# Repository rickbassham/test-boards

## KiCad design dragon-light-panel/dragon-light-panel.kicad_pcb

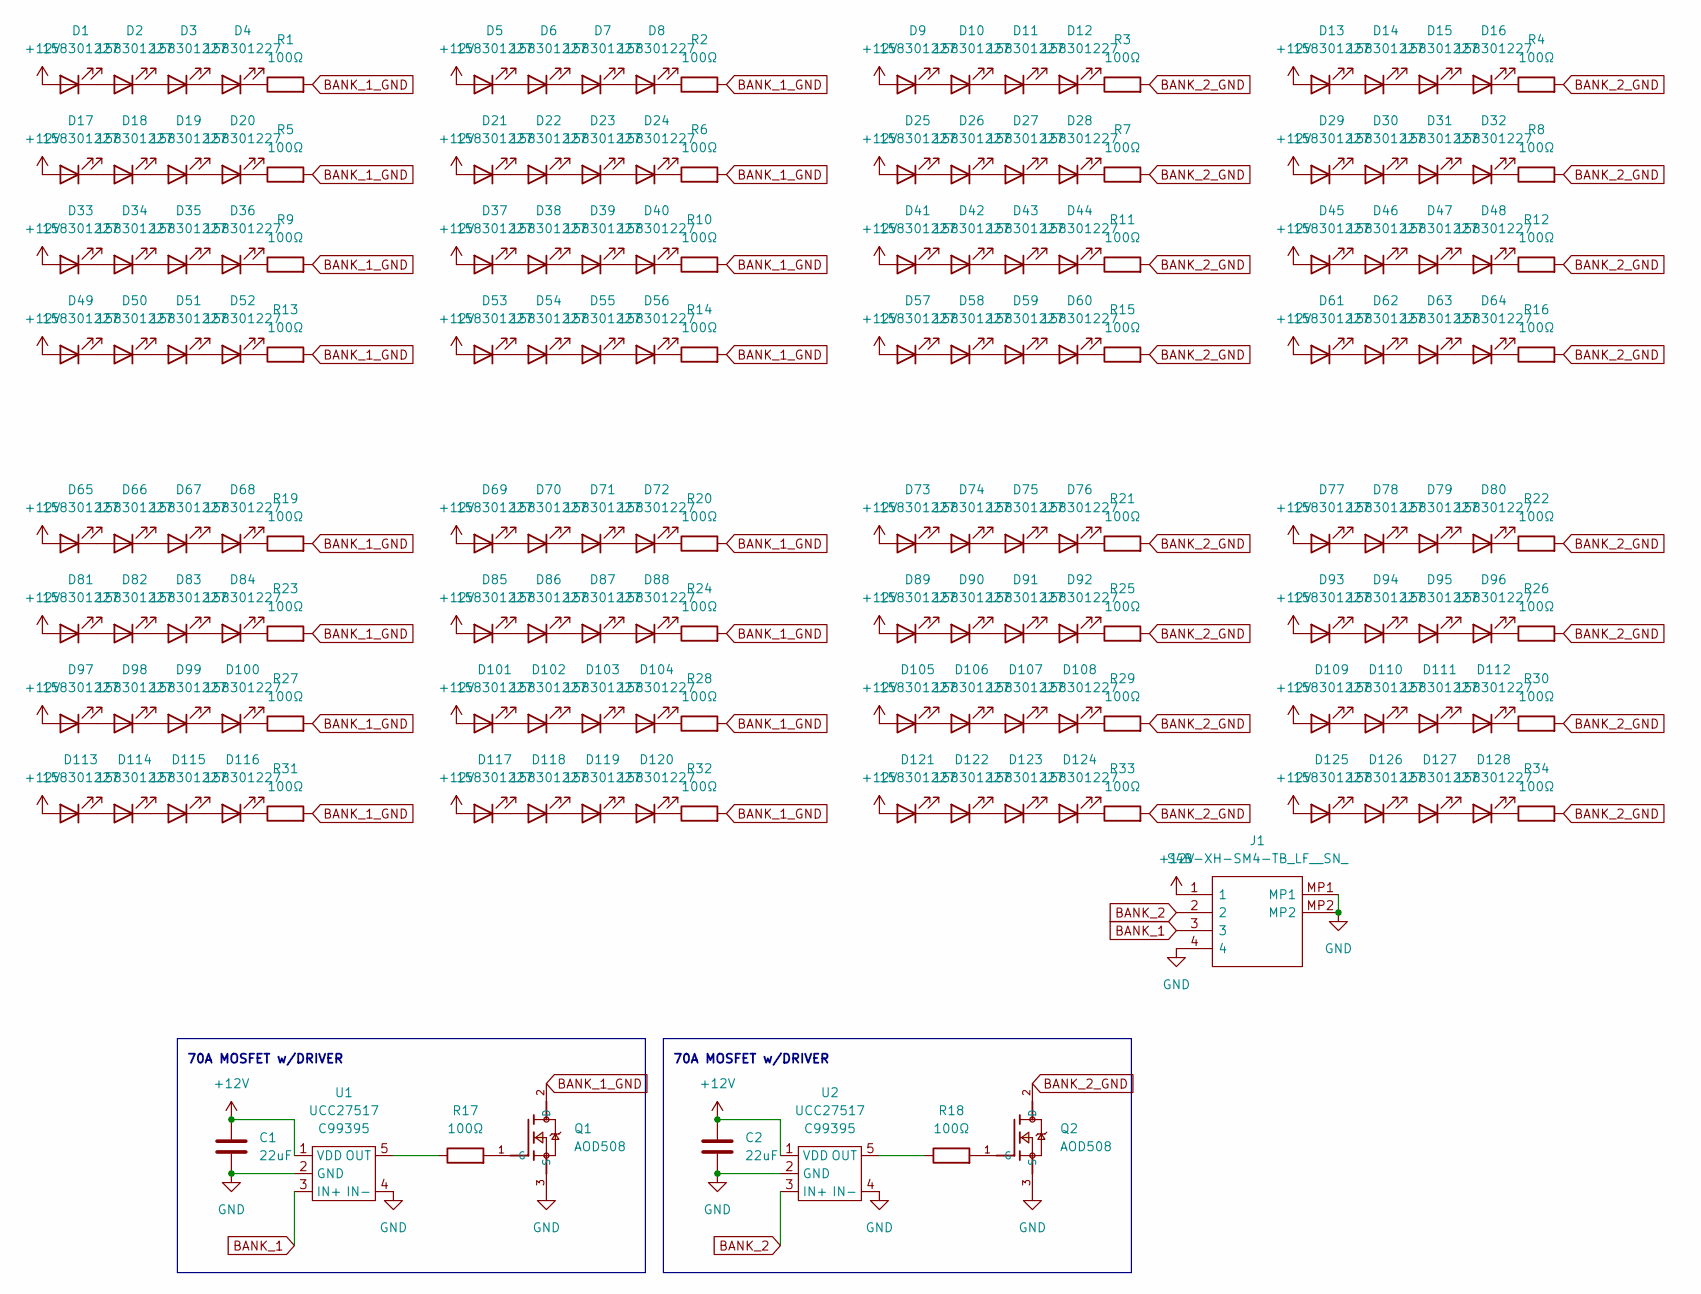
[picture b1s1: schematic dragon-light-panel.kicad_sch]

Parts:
C1, C2: 22uF; C_0805_2012Metric; LCSC C45783
D1, D2, D3, D4, D5, D6, D7, D8, D9, D10, D11, D12, D13, D14, D15, D16, D17, D18, D19, D20, D21, D22, D23, D24, D25, D26, D27, D28, D29, D30, D31, D32, D33, D34, D35, D36, D37, D38, D39, D40, D41, D42, D43, D44, D45, D46, D47, D48, D49, D50, D51, D52, D53, D54, D55, D56, D57, D58, D59, D60, D61, D62, D63, D64, D65, D66, D67, D68, D69, D70, D71, D72, D73, D74, D75, D76, D77, D78, D79, D80, D81, D82, D83, D84, D85, D86, D87, D88, D89, D90, D91, D92, D93, D94, D95, D96, D97, D98, D99, D100, D101, D102, D103, D104, D105, D106, D107, D108, D109, D110, D111, D112, D113, D114, D115, D116, D117, D118, D119, D120, D121, D122, D123, D124, D125, D126, D127, D128: 158301227; LED_1206_3216Metric; JLCPCB Class E
J1: S4B-XH-SM4-TB_LF__SN_; S4BXHSM4TBLFSN; LCSC C161861
Q1, Q2: AOD508; TO-252-2; LCSC C80964
R1, R2, R3, R4, R5, R6, R7, R8, R9, R10, R11, R12, R13, R14, R15, R16, R19, R20, R21, R22, R23, R24, R25, R26, R27, R28, R29, R30, R31, R32, R33, R34: 100Ω; R_1206_3216Metric; LCSC C17901
R17, R18: 100Ω; R_0402_1005Metric; LCSC C25076
U1, U2: UCC27517; SOT-23-5; LCSC C99395

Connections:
+12V: C1.1, C2.1, D1.2 (A), D5.2 (A), D9.2 (A), D13.2 (A), D17.2 (A), D21.2 (A), D25.2 (A), D29.2 (A), D33.2 (A), D37.2 (A), D41.2 (A), D45.2 (A), D49.2 (A), D53.2 (A), D57.2 (A), D61.2 (A), D65.2 (A), D69.2 (A), D73.2 (A), D77.2 (A), D81.2 (A), D85.2 (A), D89.2 (A), D93.2 (A), D97.2 (A), D101.2 (A), D105.2 (A), D109.2 (A), D113.2 (A), D117.2 (A), D121.2 (A), D125.2 (A), J1.1, U1.1 (VDD), U2.1 (VDD)
BANK_1: J1.3, U1.3 (IN+)
BANK_1_GND: Q1.2 (D), R1.2, R2.2, R5.2, R6.2, R9.2, R10.2, R13.2, R14.2, R19.2, R20.2, R23.2, R24.2, R27.2, R28.2, R31.2, R32.2
BANK_2: J1.2, U2.3 (IN+)
BANK_2_GND: Q2.2 (D), R3.2, R4.2, R7.2, R8.2, R11.2, R12.2, R15.2, R16.2, R21.2, R22.2, R25.2, R26.2, R29.2, R30.2, R33.2, R34.2
GND: C1.2, C2.2, J1.4, J1.MP1, J1.MP2, Q1.3 (S), Q2.3 (S), U1.2 (GND), U1.4 (IN-), U2.2 (GND), U2.4 (IN-)
unnamed: D1.1 (K), D2.2 (A)
unnamed: D2.1 (K), D3.2 (A)
unnamed: D3.1 (K), D4.2 (A)
unnamed: D4.1 (K), R1.1
unnamed: D5.1 (K), D6.2 (A)
unnamed: D6.1 (K), D7.2 (A)
unnamed: D7.1 (K), D8.2 (A)
unnamed: D8.1 (K), R2.1
unnamed: D10.1 (K), D11.2 (A)
unnamed: D9.1 (K), D10.2 (A)
unnamed: D11.1 (K), D12.2 (A)
unnamed: D12.1 (K), R3.1
unnamed: D13.1 (K), D14.2 (A)
unnamed: D14.1 (K), D15.2 (A)
unnamed: D15.1 (K), D16.2 (A)
unnamed: D16.1 (K), R4.1
unnamed: D17.1 (K), D18.2 (A)
unnamed: D18.1 (K), D19.2 (A)
unnamed: D19.1 (K), D20.2 (A)
unnamed: D20.1 (K), R5.1
unnamed: D21.1 (K), D22.2 (A)
unnamed: D22.1 (K), D23.2 (A)
unnamed: D23.1 (K), D24.2 (A)
unnamed: D24.1 (K), R6.1
unnamed: D25.1 (K), D26.2 (A)
unnamed: D26.1 (K), D27.2 (A)
unnamed: D27.1 (K), D28.2 (A)
unnamed: D28.1 (K), R7.1
unnamed: D29.1 (K), D30.2 (A)
unnamed: D30.1 (K), D31.2 (A)
unnamed: D31.1 (K), D32.2 (A)
unnamed: D32.1 (K), R8.1
unnamed: D33.1 (K), D34.2 (A)
unnamed: D34.1 (K), D35.2 (A)
unnamed: D35.1 (K), D36.2 (A)
unnamed: D36.1 (K), R9.1
unnamed: D37.1 (K), D38.2 (A)
unnamed: D38.1 (K), D39.2 (A)
unnamed: D39.1 (K), D40.2 (A)
unnamed: D40.1 (K), R10.1
unnamed: D41.1 (K), D42.2 (A)
unnamed: D42.1 (K), D43.2 (A)
unnamed: D43.1 (K), D44.2 (A)
unnamed: D44.1 (K), R11.1
unnamed: D45.1 (K), D46.2 (A)
unnamed: D46.1 (K), D47.2 (A)
unnamed: D47.1 (K), D48.2 (A)
unnamed: D48.1 (K), R12.1
unnamed: D49.1 (K), D50.2 (A)
unnamed: D50.1 (K), D51.2 (A)
unnamed: D51.1 (K), D52.2 (A)
unnamed: D52.1 (K), R13.1
unnamed: D53.1 (K), D54.2 (A)
unnamed: D54.1 (K), D55.2 (A)
unnamed: D55.1 (K), D56.2 (A)
unnamed: D56.1 (K), R14.1
unnamed: D57.1 (K), D58.2 (A)
unnamed: D58.1 (K), D59.2 (A)
unnamed: D59.1 (K), D60.2 (A)
unnamed: D60.1 (K), R15.1
unnamed: D61.1 (K), D62.2 (A)
unnamed: D62.1 (K), D63.2 (A)
unnamed: D63.1 (K), D64.2 (A)
unnamed: D64.1 (K), R16.1
unnamed: D65.1 (K), D66.2 (A)
unnamed: D66.1 (K), D67.2 (A)
unnamed: D67.1 (K), D68.2 (A)
unnamed: D68.1 (K), R19.1
unnamed: D69.1 (K), D70.2 (A)
unnamed: D70.1 (K), D71.2 (A)
unnamed: D71.1 (K), D72.2 (A)
unnamed: D72.1 (K), R20.1
unnamed: D73.1 (K), D74.2 (A)
unnamed: D74.1 (K), D75.2 (A)
unnamed: D75.1 (K), D76.2 (A)
unnamed: D76.1 (K), R21.1
unnamed: D77.1 (K), D78.2 (A)
unnamed: D78.1 (K), D79.2 (A)
unnamed: D79.1 (K), D80.2 (A)
unnamed: D80.1 (K), R22.1
unnamed: D81.1 (K), D82.2 (A)
unnamed: D82.1 (K), D83.2 (A)
unnamed: D83.1 (K), D84.2 (A)
unnamed: D84.1 (K), R23.1
unnamed: D85.1 (K), D86.2 (A)
unnamed: D86.1 (K), D87.2 (A)
unnamed: D87.1 (K), D88.2 (A)
unnamed: D88.1 (K), R24.1
unnamed: D89.1 (K), D90.2 (A)
unnamed: D90.1 (K), D91.2 (A)
unnamed: D91.1 (K), D92.2 (A)
unnamed: D92.1 (K), R25.1
unnamed: D93.1 (K), D94.2 (A)
unnamed: D94.1 (K), D95.2 (A)
unnamed: D95.1 (K), D96.2 (A)
unnamed: D96.1 (K), R26.1
unnamed: D97.1 (K), D98.2 (A)
unnamed: D98.1 (K), D99.2 (A)
unnamed: D100.1 (K), R27.1
unnamed: D99.1 (K), D100.2 (A)
unnamed: D101.1 (K), D102.2 (A)
unnamed: D102.1 (K), D103.2 (A)
unnamed: D103.1 (K), D104.2 (A)
unnamed: D104.1 (K), R28.1
unnamed: D105.1 (K), D106.2 (A)
unnamed: D106.1 (K), D107.2 (A)
unnamed: D107.1 (K), D108.2 (A)
unnamed: D108.1 (K), R29.1
unnamed: D109.1 (K), D110.2 (A)
unnamed: D110.1 (K), D111.2 (A)
unnamed: D111.1 (K), D112.2 (A)
unnamed: D112.1 (K), R30.1
unnamed: D113.1 (K), D114.2 (A)
unnamed: D114.1 (K), D115.2 (A)
unnamed: D115.1 (K), D116.2 (A)
unnamed: D116.1 (K), R31.1
unnamed: D117.1 (K), D118.2 (A)
unnamed: D118.1 (K), D119.2 (A)
unnamed: D119.1 (K), D120.2 (A)
unnamed: D120.1 (K), R32.1
unnamed: D121.1 (K), D122.2 (A)
unnamed: D122.1 (K), D123.2 (A)
unnamed: D123.1 (K), D124.2 (A)
unnamed: D124.1 (K), R33.1
unnamed: D125.1 (K), D126.2 (A)
unnamed: D126.1 (K), D127.2 (A)
unnamed: D127.1 (K), D128.2 (A)
unnamed: D128.1 (K), R34.1
unnamed: Q1.1 (G), R17.2
unnamed: Q2.1 (G), R18.2
unnamed: R17.1, U1.5 (OUT)
unnamed: R18.1, U2.5 (OUT)

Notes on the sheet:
70A MOSFET w/DRIVER

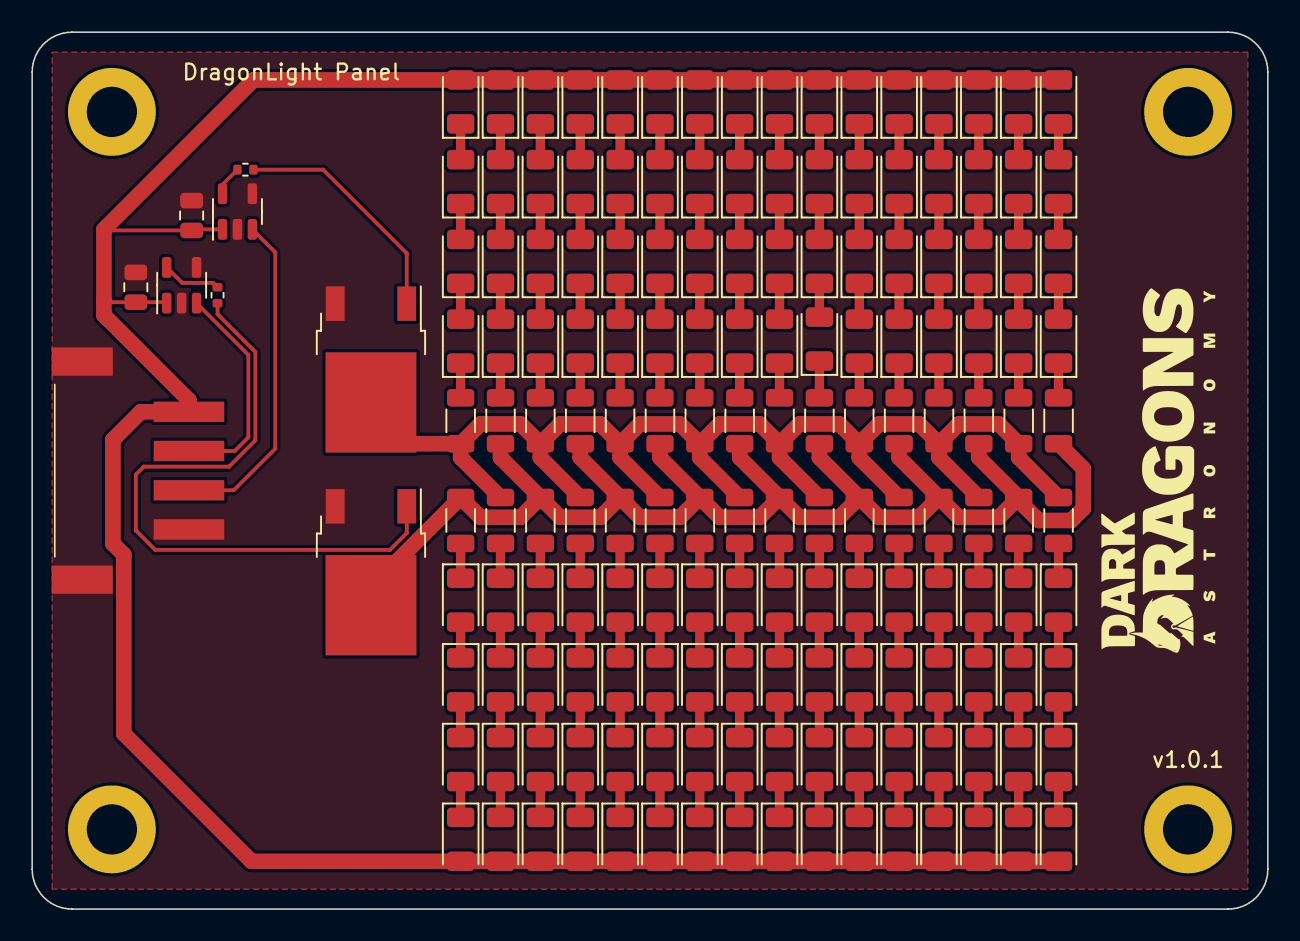
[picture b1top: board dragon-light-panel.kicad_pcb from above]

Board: 2 copper layers, 78.7 x 55.9 mm, 173 parts (0 on the bottom side), 138 nets.

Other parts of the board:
H1, H2, H3, H4: MountingHole_Pad; MountingHole_3.2mm_M3_DIN965_Pad

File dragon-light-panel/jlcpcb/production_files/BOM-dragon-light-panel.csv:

Comment,Designator,Footprint,LCSC
100Ω,"R1,R10,R11,R12,R13,R14,R15,R16,R2,R3,R4,R5,R6,R7,R8,R9",R_1206_3216Metric,C17901
100Ω,"R17,R18",R_0402_1005Metric,C25076
22uF,"C1,C2",C_0805_2012Metric,C45783
AOD508,"Q1,Q2",TO-252-2,C80964
UCC27517,"U1,U2",SOT-23-5,C99395
158301227,D1,LED_1206_3216Metric,
158301227,D23,LED_1206_3216Metric,
158301227,D16,LED_1206_3216Metric,
158301227,D11,LED_1206_3216Metric,
158301227,D47,LED_1206_3216Metric,
158301227,D57,LED_1206_3216Metric,
158301227,D44,LED_1206_3216Metric,
158301227,D52,LED_1206_3216Metric,
158301227,D49,LED_1206_3216Metric,
158301227,D15,LED_1206_3216Metric,
158301227,D17,LED_1206_3216Metric,
158301227,D34,LED_1206_3216Metric,
158301227,D19,LED_1206_3216Metric,
158301227,D26,LED_1206_3216Metric,
158301227,D6,LED_1206_3216Metric,
158301227,D41,LED_1206_3216Metric,
158301227,D22,LED_1206_3216Metric,
158301227,D45,LED_1206_3216Metric,
158301227,D63,LED_1206_3216Metric,
158301227,D3,LED_1206_3216Metric,
158301227,D21,LED_1206_3216Metric,
158301227,D64,LED_1206_3216Metric,
158301227,D32,LED_1206_3216Metric,
158301227,D56,LED_1206_3216Metric,
158301227,D50,LED_1206_3216Metric,
158301227,D61,LED_1206_3216Metric,
158301227,D28,LED_1206_3216Metric,
158301227,D35,LED_1206_3216Metric,
158301227,D2,LED_1206_3216Metric,
158301227,D9,LED_1206_3216Metric,
158301227,D33,LED_1206_3216Metric,
158301227,D14,LED_1206_3216Metric,
158301227,D46,LED_1206_3216Metric,
158301227,D7,LED_1206_3216Metric,
MountingHole_Pad,H3,MountingHole_3.2mm_M3_DIN965_Pad,
158301227,D29,LED_1206_3216Metric,
158301227,D36,LED_1206_3216Metric,
158301227,D42,LED_1206_3216Metric,
158301227,D43,LED_1206_3216Metric,
158301227,D24,LED_1206_3216Metric,
MountingHole_Pad,H2,MountingHole_3.2mm_M3_DIN965_Pad,
158301227,D55,LED_1206_3216Metric,
158301227,D37,LED_1206_3216Metric,
158301227,D58,LED_1206_3216Metric,
158301227,D12,LED_1206_3216Metric,
158301227,D30,LED_1206_3216Metric,
MountingHole_Pad,H1,MountingHole_3.2mm_M3_DIN965_Pad,
158301227,D25,LED_1206_3216Metric,
158301227,D53,LED_1206_3216Metric,
158301227,D18,LED_1206_3216Metric,
158301227,D60,LED_1206_3216Metric,
158301227,D27,LED_1206_3216Metric,
158301227,D8,LED_1206_3216Metric,
158301227,D4,LED_1206_3216Metric,
158301227,D20,LED_1206_3216Metric,
158301227,D5,LED_1206_3216Metric,
158301227,D59,LED_1206_3216Metric,
158301227,D38,LED_1206_3216Metric,
158301227,D39,LED_1206_3216Metric,
158301227,D10,LED_1206_3216Metric,
MountingHole_Pad,H4,MountingHole_3.2mm_M3_DIN965_Pad,
158301227,D40,LED_1206_3216Metric,
158301227,D62,LED_1206_3216Metric,
158301227,D51,LED_1206_3216Metric,
158301227,D54,LED_1206_3216Metric,
Conn_01x04,J1,JST_XH_B4B-XH-A_1x04_P2.50mm_Vertical,
158301227,D13,LED_1206_3216Metric,
158301227,D48,LED_1206_3216Metric,
158301227,D31,LED_1206_3216Metric,

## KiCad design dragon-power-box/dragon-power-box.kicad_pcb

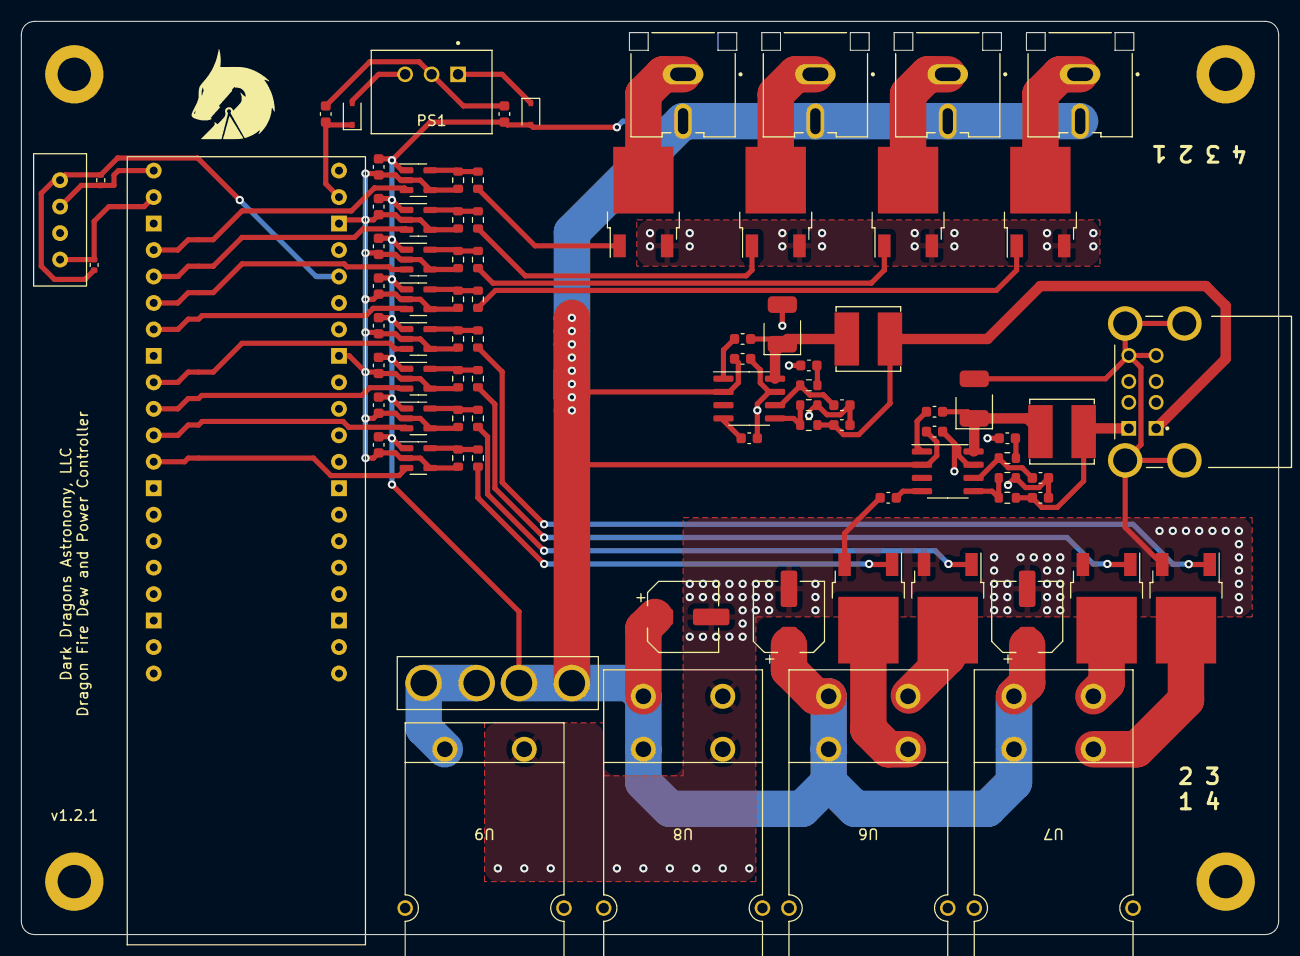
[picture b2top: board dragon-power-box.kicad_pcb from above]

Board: 2 copper layers, 120.7 x 87.6 mm, 100 parts (0 on the bottom side), 65 nets.

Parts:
C1, C2, C3, C4, C5, C6, C7, C8, C10, C16, C41: 22uF; C_0603_1608Metric
C9, C15: 100nF; C_0603_1608Metric
C11, C17: 47uF; C_0603_1608Metric
C12, C18: 10pF; C_0603_1608Metric
C13, C19: 1nF; C_0603_1608Metric
C14, C20: 8.2nF; C_0603_1608Metric
C38, C39, C40: 470uF; CP_Elec_6.3x7.7
C42: 10uF; C_0603_1608Metric
D1, D4: SS54
D2: BAT60A; D_SOD-323
D3: 1N5819WS; D_SOD-323
F1: Fuse; Keystone 3522-2 Fuse Holder
H1, H2, H3, H4: MountingHole_Pad; MountingHole_3.2mm_M3_DIN965_Pad
J1, J2, J3, J4: RCJ-044; CUI_RCJ-044
J5: 1903815-1; TE_1903815-1
L1, L2: L_Iron; L_Bourns_SRN6045TA
NT1, NT2, NT3, NT4, NT5, NT6, NT7, NT8, NT9, NT10: NetTie_2; NetTie-2_SMD_Pad0.5mm
PS1: P78E05-1000; CONV_P78E05-1000
Q1, Q2, Q3, Q4, Q5, Q6, Q7, Q8: AOD508; TO-252-2
R1, R2, R5, R6, R9, R10, R13, R14: 100Ω; R_0603_1608Metric
R3, R4, R7, R8, R11, R12, R15, R16: 10kΩ; R_0603_1608Metric
R17, R20: 10.2kΩ; R_0603_1608Metric
R18, R21: 61.9kΩ; R_0603_1608Metric
R19, R22: 1.96kΩ; R_0603_1608Metric
R29, R31: 10k; R_0402_1005Metric
U1: WIZNET-W5100; w5100s-evb-pico-no-debug
U2, U3, U4, U24, U25, U26, U27, U28: UCC27517; SOT-23-5
U5: AM2320
U6, U7, U8: PP25-1317G12-1317G11-BK-DOUBLE
U9: PP25-1317G12-BK
U29, U30: TPS54331DR; SOIC-8_3.9x4.9mm_P1.27mm

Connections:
12V_IN_1: NT10.2, U24.3 (IN+)
12V_IN_2: NT9.2, U3.3 (IN+)
12V_IN_3: NT8.2, U4.3 (IN+)
12V_IN_4: NT7.2, U2.3 (IN+)
12V_OUT_1: Q4.2 (D), U6.2 (BLACK)
12V_OUT_2: Q2.2 (D), U6.4 (BLACK)
12V_OUT_3: Q3.2 (D), U7.4 (BLACK)
12V_OUT_4: Q1.2 (D), U7.2 (BLACK)
+3V3: R29.1, R31.2, U1.36 (3V3), U5.1 (PWR)
+5V: C41.1, D2.1 (K), U1.39 (VSYS)
+12V: C1.1, C2.1, C3.1, C4.1, C5.1, C6.1, C7.1, C8.1, C10.1, C16.1, C38.1, C39.1, C40.1, C42.1, D3.2 (A), F1.1, J1.2, J2.2, J3.2, J4.2, U2.1 (VDD), U3.1 (VDD), U4.1 (VDD), U6.1 (RED), U6.3 (RED), U7.1 (RED), U7.3 (RED), U8.1 (RED), U8.3 (RED), U24.1 (VDD), U25.1 (VDD), U26.1 (VDD), U27.1 (VDD), U28.1 (VDD), U29.2 (VIN), U30.2 (VIN)
/Power/12V_PRE_FUSED: F1.2, U9.1 (RED)
GND: C1.2, C2.2, C3.2, C4.2, C5.2, C6.2, C7.2, C8.2, C10.2, C11.2, C12.2, C13.2, C14.2, C16.2, C17.2, C18.2, C19.2, C20.2, C38.2, C39.2, C40.2, C41.2, C42.2, D1.2 (A), D4.2 (A), J5.4 (GND2), J5.8 (GND1), J5.P1 (SHIELD), J5.P2 (SHIELD), J5.P3 (SHIELD), J5.P4 (SHIELD), PS1.2 (GND/-VOUT), Q1.3 (S), Q2.3 (S), Q3.3 (S), Q4.3 (S), Q5.3 (S), Q6.3 (S), Q7.3 (S), Q8.3 (S), R3.1, R4.1, R7.1, R8.1, R11.1, R12.1, R15.1, R16.1, R19.2, R22.2, U1.3 (GND), U1.8 (GND), U1.13 (GND), U1.18 (GND), U1.23 (GND), U1.28 (GND), U1.33 (GND), U1.38 (GND), U2.2 (GND), U2.4 (IN-), U3.2 (GND), U3.4 (IN-), U4.2 (GND), U4.4 (IN-), U5.3 (GND), U8.2 (BLACK), U8.4 (BLACK), U9.2 (BLACK), U24.2 (GND), U24.4 (IN-), U25.2 (GND), U25.4 (IN-), U26.2 (GND), U26.4 (IN-), U27.2 (GND), U27.4 (IN-), U28.2 (GND), U28.4 (IN-), U29.7 (GND), U30.7 (GND)
GPIO_0: NT1.1, U1.1 (GP0)
GPIO_1: NT2.1, U1.2 (GP1)
GPIO_2: NT3.1, U1.4 (GP2)
GPIO_3: NT4.1, U1.5 (GP3)
GPIO_4: NT5.1, U1.6 (GP4)
GPIO_5: NT6.1, U1.7 (GP5)
GPIO_6: NT7.1, U1.9 (GP6)
GPIO_7: NT8.1, U1.10 (GP7)
GPIO_8: NT9.1, U1.11 (GP8)
GPIO_9: NT10.1, U1.12 (GP9)
unnamed: C9.1, U29.1 (BOOT)
unnamed: C9.2, D1.1 (K), L1.1, U29.8 (PH)
unnamed: C12.1, R18.1, U29.6 (COMP)
unnamed: C13.1, R18.2
unnamed: C14.1, U29.4 (SS)
unnamed: C15.1, U30.1 (BOOT)
unnamed: C15.2, D4.1 (K), L2.1, U30.8 (PH)
unnamed: C18.1, R21.1, U30.6 (COMP)
unnamed: C19.1, R21.2
unnamed: C20.1, U30.4 (SS)
unnamed: D2.2 (A), PS1.3 (+VOUT/GND)
unnamed: D3.1 (K), PS1.1 (+VIN)
unnamed: Q1.1 (G), R1.2
unnamed: Q2.1 (G), R2.2
unnamed: Q3.1 (G), R5.2
unnamed: Q4.1 (G), R6.2
unnamed: Q5.1 (G), R9.2
unnamed: Q6.1 (G), R10.2
unnamed: Q7.1 (G), R13.2
unnamed: Q8.1 (G), R14.2
unnamed: R1.1, R3.2, U2.5 (OUT)
unnamed: R2.1, R4.2, U3.5 (OUT)
unnamed: R5.1, R7.2, U4.5 (OUT)
unnamed: R6.1, R8.2, U24.5 (OUT)
unnamed: R10.1, R12.2, U26.5 (OUT)
unnamed: R9.1, R11.2, U25.5 (OUT)
unnamed: R13.1, R15.2, U27.5 (OUT)
unnamed: R14.1, R16.2, U28.5 (OUT)
unnamed: R17.2, R19.1, U29.5 (VSENSE)
unnamed: R20.2, R22.1, U30.5 (VSENSE)
PWM_IN_1: NT3.2, U25.3 (IN+)
PWM_IN_2: NT4.2, U27.3 (IN+)
PWM_IN_3: NT5.2, U26.3 (IN+)
PWM_IN_4: NT6.2, U28.3 (IN+)
PWM_OUT_1: J1.1, Q5.2 (D)
PWM_OUT_2: J2.1, Q7.2 (D)
PWM_OUT_3: J3.1, Q6.2 (D)
PWM_OUT_4: J4.1, Q8.2 (D)
SCL: NT2.2, R31.1, U5.4 (SCL)
SDA: NT1.2, R29.2, U5.2 (SDA)
USB_5V_1: C11.1, J5.5 (VBUS1), L1.2, R17.1
USB_5V_2: C17.1, J5.1 (VBUS2), L2.2, R20.1

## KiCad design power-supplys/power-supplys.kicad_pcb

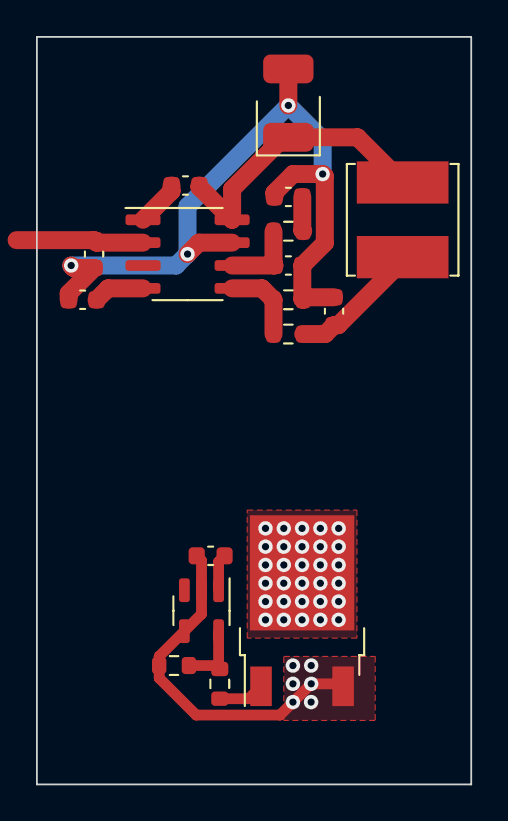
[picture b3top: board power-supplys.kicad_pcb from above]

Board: 2 copper layers, 24.1 x 41.5 mm, 17 parts (0 on the bottom side), 11 nets.

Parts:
C1, C7: 22uF; C_0603_1608Metric
C2: 100nF; C_0603_1608Metric
C3: 47uF; C_0603_1608Metric
C4: 1nF; C_0603_1608Metric
C5: 10pF; C_0603_1608Metric
C6: 8.2nF; C_0603_1608Metric
D1: SS54
L1: L_Iron; L_Bourns_SRN6045TA
Q1: AOD508; TO-252-2
R1: 10.2kΩ; R_0603_1608Metric
R2: 61.9kΩ; R_0603_1608Metric
R3: 1.96kΩ; R_0603_1608Metric
R4: 100Ω; R_0603_1608Metric
R5: 10kΩ; R_0603_1608Metric
U1: TPS54331DR; SOIC-8_3.9x4.9mm_P1.27mm
U2: UCC27517; SOT-23-5

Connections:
+5V: C3.1, L1.2, R1.1
+12V: C1.1, C7.1, U1.2 (VIN), U2.1 (VDD)
GND: C1.2, C3.2, C4.2, C5.2, C6.2, C7.2, D1.2 (A), Q1.3 (S), R3.2, R5.1, U1.7 (GND), U2.2 (GND), U2.4 (IN-)
unnamed: C6.1, U1.4 (SS)
unnamed: Q1.1 (G), R4.2
unnamed: R1.2, R3.1, U1.5 (VSENSE)
unnamed: C5.1, R2.1, U1.6 (COMP)
unnamed: C4.1, R2.2
unnamed: R4.1, R5.2, U2.5 (OUT)
unnamed: C2.1, U1.1 (BOOT)
unnamed: C2.2, D1.1 (K), L1.1, U1.8 (PH)

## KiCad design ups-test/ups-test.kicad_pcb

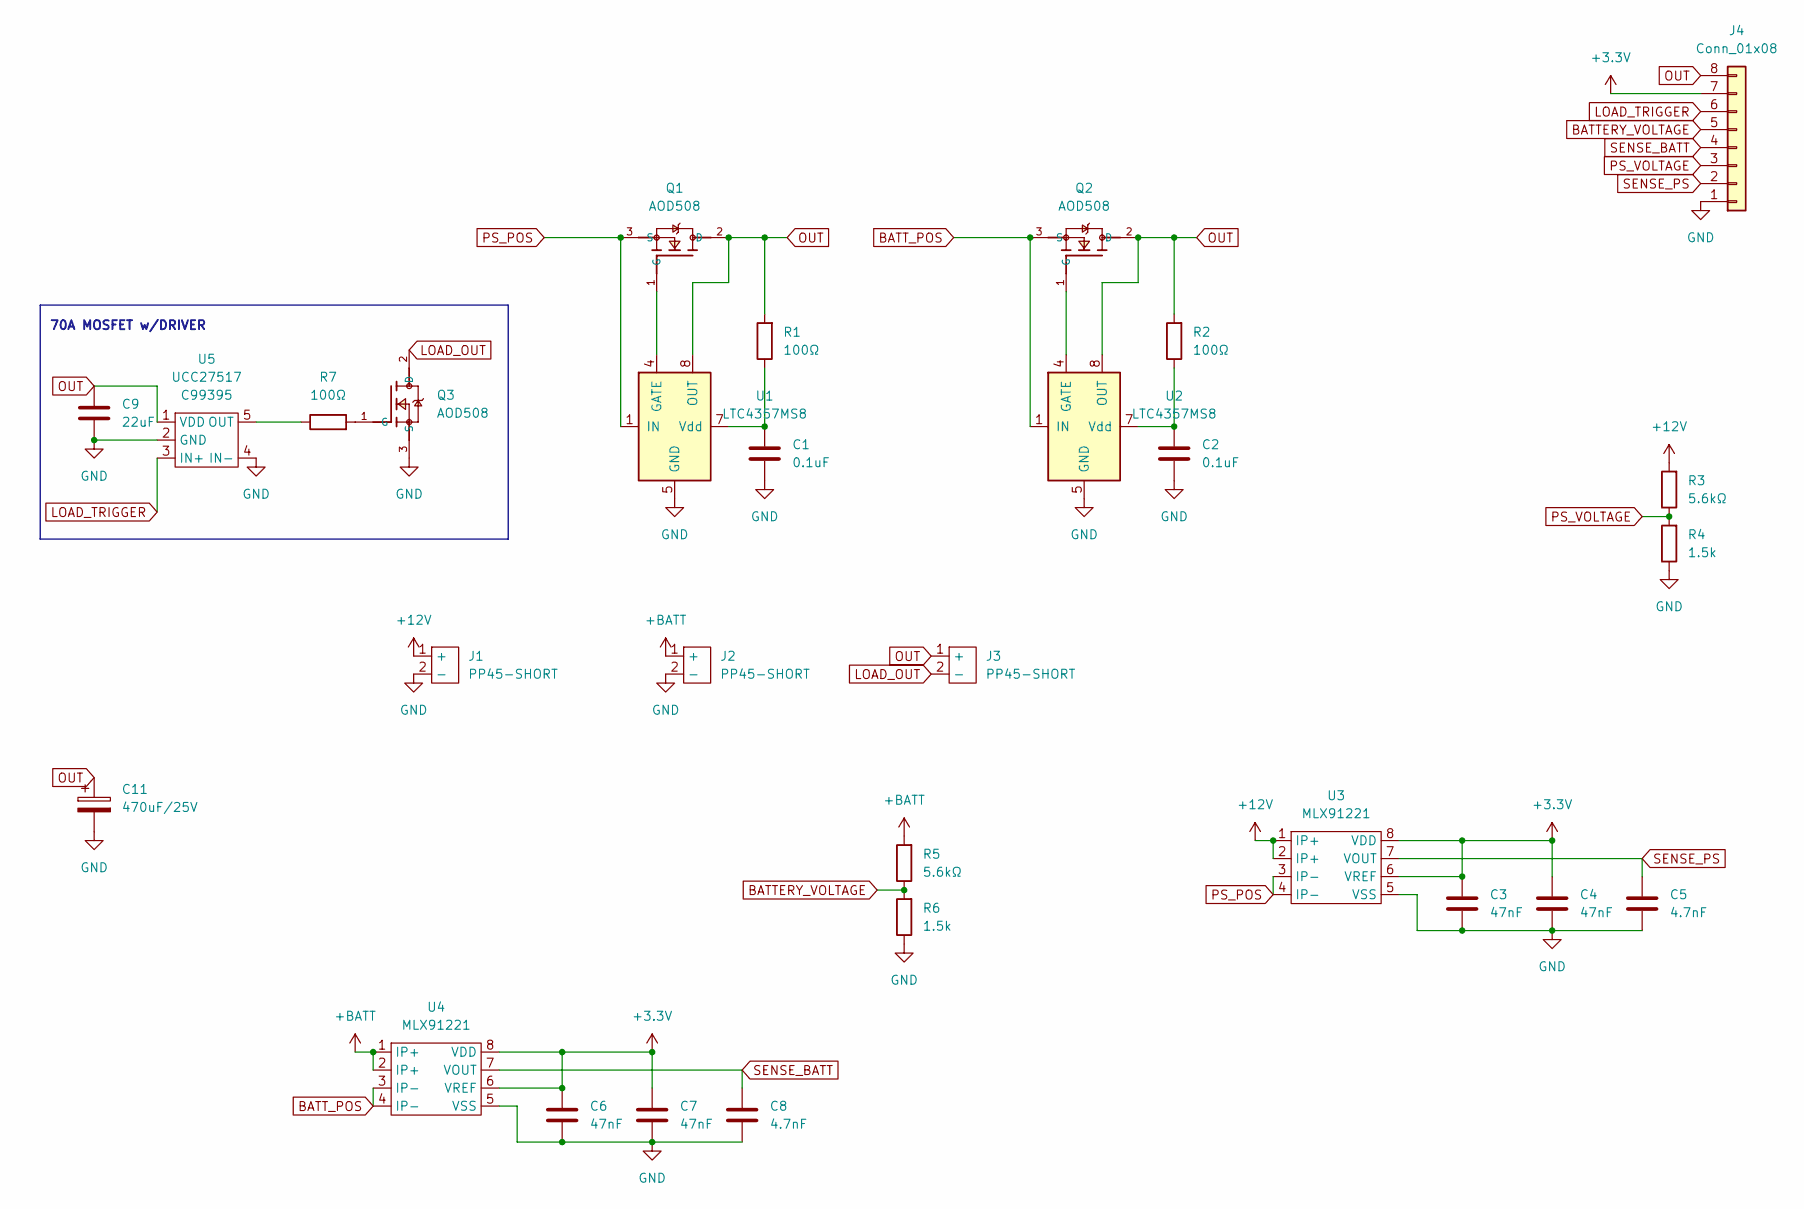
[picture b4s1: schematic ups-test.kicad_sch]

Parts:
C1, C2: 0.1uF; C_0402_1005Metric; LCSC C1525
C3, C4, C6, C7: 47nF; C_0603_1608Metric; LCSC C1622
C5, C8: 4.7nF; C_0603_1608Metric; LCSC C53987
C9: 22uF; C_0805_2012Metric; LCSC C45783
C11: 470uF/25V; CP_Elec_10x10.5; LCSC C242138
J1, J2, J3: PP45-SHORT
J4: Conn_01x08; PinHeader_1x08_P2.54mm_Vertical
Q1, Q2, Q3: AOD508; TO-252-2; LCSC C80964
R1, R2: 100Ω; R_0402_1005Metric; LCSC C25076
R3, R5: 5.6kΩ; R_0805_2012Metric; LCSC C4382
R4, R6: 1.5k; R_0805_2012Metric; LCSC C4310
R7: 100Ω; R_0603_1608Metric; LCSC C22775
U1, U2: LTC4357MS8; MSOP-8_3x3mm_P0.65mm
U3, U4: MLX91221; SOIC-8_3.9x4.9mm_P1.27mm
U5: UCC27517; SOT-23-5; LCSC C99395

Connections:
+3V3: C3.1, C4.1, C6.1, C7.1, J4.7, U3.6 (VREF), U3.8 (VDD), U4.6 (VREF), U4.8 (VDD)
+12V: J1.1 (+), R3.2, U3.1 (IP+), U3.2 (IP+)
+BATT: J2.1 (+), R5.2, U4.1 (IP+), U4.2 (IP+)
BATTERY_VOLTAGE: J4.5, R5.1, R6.2
BATT_POS: Q2.3 (S), U2.1 (IN), U4.3 (IP-), U4.4 (IP-)
GND: C1.2, C2.2, C3.2, C4.2, C5.2, C6.2, C7.2, C8.2, C9.2, C11.2, J1.2 (-), J2.2 (-), J4.1, Q3.3 (S), R4.1, R6.1, U1.5 (GND), U2.5 (GND), U3.5 (VSS), U4.5 (VSS), U5.2 (GND), U5.4 (IN-)
LOAD_OUT: J3.2 (-), Q3.2 (D)
LOAD_TRIGGER: J4.6, U5.3 (IN+)
unnamed: C1.1, R1.1, U1.7 (Vdd)
unnamed: C2.1, R2.1, U2.7 (Vdd)
unnamed: Q1.1 (G), U1.4 (GATE)
unnamed: Q2.1 (G), U2.4 (GATE)
unnamed: Q3.1 (G), R7.2
unnamed: R7.1, U5.5 (OUT)
OUT: C9.1, C11.1, J3.1 (+), J4.8, Q1.2 (D), Q2.2 (D), R1.2, R2.2, U1.8 (OUT), U2.8 (OUT), U5.1 (VDD)
PS_POS: Q1.3 (S), U1.1 (IN), U3.3 (IP-), U3.4 (IP-)
PS_VOLTAGE: J4.3, R3.1, R4.2
SENSE_BATT: C8.1, J4.4, U4.7 (VOUT)
SENSE_PS: C5.1, J4.2, U3.7 (VOUT)

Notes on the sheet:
70A MOSFET w/DRIVER

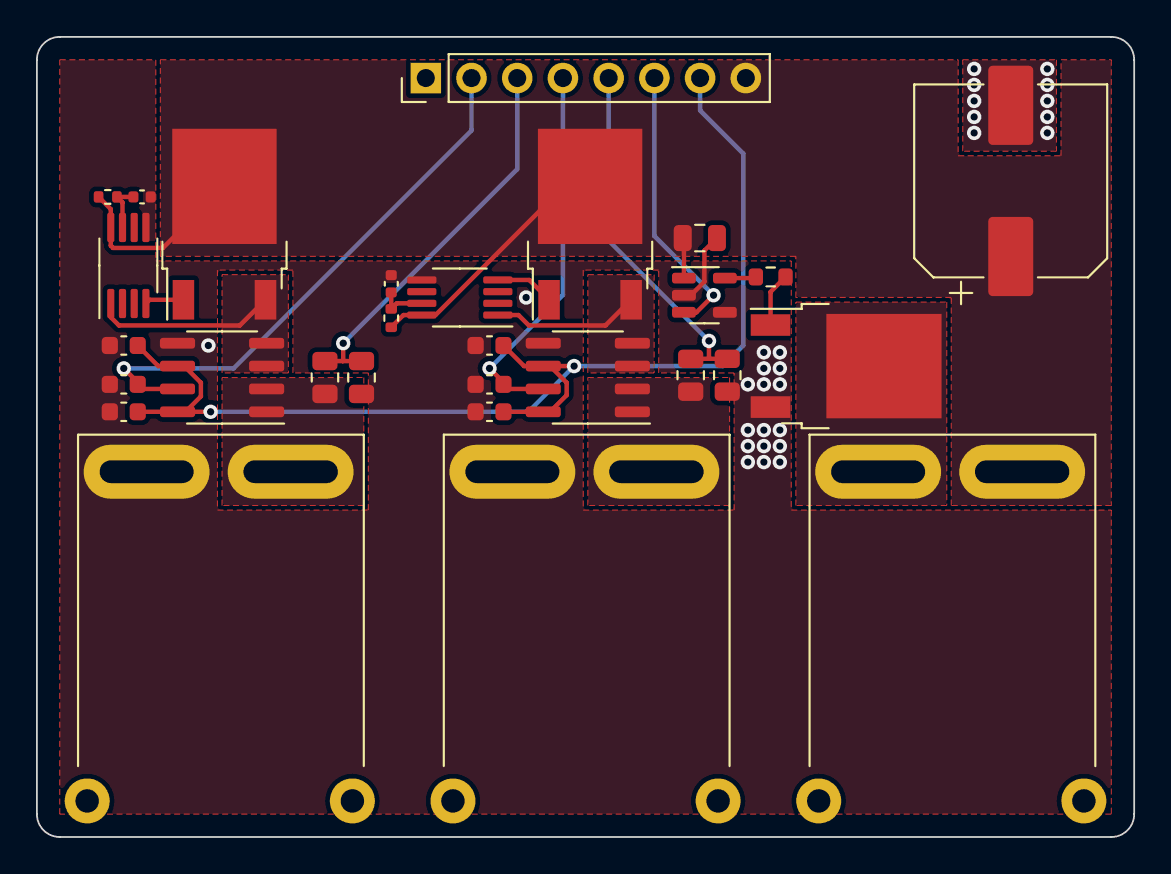
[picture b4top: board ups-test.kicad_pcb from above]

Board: 2 copper layers, 61.0 x 44.5 mm, 29 parts (0 on the bottom side), 19 nets.

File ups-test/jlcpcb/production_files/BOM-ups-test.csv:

Comment,Designator,Footprint,LCSC
0.1uF,"C1,C2",C_0402_1005Metric,C1525
47nF,"C3,C4,C6,C7",C_0603_1608Metric,C1622
100Ω,R7,R_0603_1608Metric,C22775
100Ω,"R1,R2",R_0402_1005Metric,C25076
1.5k,"R4,R6",R_0805_2012Metric,C4310
5.6kΩ,"R3,R5",R_0805_2012Metric,C4382
22uF,C9,C_0805_2012Metric,C45783
LTC4357MS8,"U1,U2",MSOP-8_3x3mm_P0.65mm,C462642
4.7nF,"C5,C8",C_0603_1608Metric,C53987
AOD508,"Q1,Q2,Q3",TO-252-2,C80964
UCC27517,U5,SOT-23-5,C99395
MLX91221,U4,SOIC-8_3.9x4.9mm_P1.27mm,
MLX91221,U3,SOIC-8_3.9x4.9mm_P1.27mm,
